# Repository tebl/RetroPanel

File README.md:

# RetroPanel
Having found a motherboard I really wanted to use, I found that obtaining an AT-case wasn't quite as easy as I had expected - at least none that met my demands for condition, price and availability anywhere near me. That's the short of it, see [Background](#2-background) for the full story. Anyway, my solution to my predicament was to simply use a slightly more modern ATX-case, but I wanted it to have all of the features available to even the earlies of computer generations available to me - that includes a working power switch, a turbo-switch and one of those awesome looking Mhz-displays. Add a clock and a temperature-sensor and it soon becomes apparent: such a thing, only had the potential to exist in my head.

So I made one.

The resulting computer isn't what I had originally intended to build, but I am quite happy with the results. There are better MBs, there are faster CPU options available and the graphics card will excite no other retro enthusiast other the one I grew into - however, it is exactly the *"right"* kind of slow for the games I remember. The *RetroPanel* was the missing piece to make all of that work, and with the wonders of *open-source* you should now have everything you need to build one as well.

- [1> Versions](#1-versions)
  - [1.1> RetroPanel](#11-retropanel)
- [2> Background](#2-background)
- [3> Resources](#3-resources)
- [4> Acknowledgements](#4-acknowledgements)

# 1> Versions
While there may only be one version of the RetroPanel for quite some time, but knowing myself and the fact that it has become a form factor that I really like - in time there will be more than one version of the RetroPanel. The differences will more than likely be in core functionality, not in terms of different faceplates that should already be catered for in the standard version.

| Module                            | Description                                      |
| --------------------------------- | ------------------------------------------------ | 
| [RetroPanel](#11-retropanel)      | Standard version

## 1.1> RetroPanel

The standard version of the RetroPanel, envisioned to provide most features found on cases from even the earlies of computer generations - that includes a working power switch, a turbo-switch and one of those awesome looking Mhz-displays. With options for installing modules for adding a clock (RTC) to it as well as a temperature-sensor (BMP280).

The standard version is composed of the following set of PCBs, in the cases of alternative faceplates you would only need the one that is suitable for your needs. Follow the documentation links for specific information related to each of them, note that the documentation on building one of these units this is covered through the documentation for the main PCB ([RetroPanel Module](https://github.com/tebl/BulkyMIDI-32/tree/main/BulkyMIDI-32%20Module)).

| PCB                 | # Required    | Description                        | Documentation                      | Order      |
| ---------------------- | ----------- | ---------------------------------- | ---------------------------------- | ---------- |
| [RetroPanel Module](https://github.com/tebl/RetroPanel/tree/main/RetroPanel%20Module) | 1 | Main module | [Documentation](https://github.com/tebl/RetroPanel/blob/main/RetroPanel%20Module/README.md), [BOM](https://github.com/tebl/RetroPanel/blob/main/RetroPanel%20Module/README.md#3-bom) | PCBWay
| [RetroPanel Front](https://github.com/tebl/RetroPanel/tree/main/RetroPanel%20Front) | 1 | Front-facing board holding components | [Documentation](https://github.com/tebl/RetroPanel/blob/main/RetroPanel%20Front/README.md), [BOM](https://github.com/tebl/RetroPanel/blob/main/RetroPanel%20Front/README.md#3-bom) | PCBWay
| [RetroPanel Side](https://github.com/tebl/RetroPanel/tree/main/RetroPanel%20Side) | 2 | Design for the sides, you need two of these. | [Documentation](https://github.com/tebl/RetroPanel/blob/main/RetroPanel%20Side/README.md) | PCBWay
| [RetroPanel Faceplate (FP1)](https://github.com/tebl/RetroPanel/tree/main/faceplates/RetroPanel%20FP1) | 1 | Faceplate that goes on the very front of the module, this has provisions for all switches and LEDs | [Documentation](https://github.com/tebl/RetroPanel/tree/main/faceplates/RetroPanel%20FP1) | PCBWay

# 2> Background
Recently I had the glorious idea of rebuilding the first PC I bought, it was a low-budget option put together from a list of parts in the later parts of 1995. Due to sheer luck I still had some driver disks that came with it, so I knew that what I was looking for was a motherboard with the model number *P51437P4/FMB* as well as a *Cirrus Logic 5436* graphics card. Surprisingly expensive, no doubt because noone had felt like keeping the super-cheap hardware options in the first place - additionally it was an AT-motherboard with one of those clocks that you couldn't exchange the battery for.

Why does that matter? It doesn't, but the next thing does: I couldn't find an AT-case that wasn't either horribly mangled, situated around a collectors more beloved hardware or any combination of the two. Well, that's not completely true - I found and bought a case, but it was thrown from every moving postal truck from Poland all the way up to where I live - bringing us back to the first point on my little list.

No doubt having already listened in on my internal dialogue, YouTube gave me a viewing recommendation for a video from [philscomputerlab](https://www.youtube.com/@philscomputerlab) - [Building the 486 DX2 66 Retro Sleeper DOS PC](https://youtu.be/9bqqpuJ7M_I). What I liked with it was that he gave me a viable option by gently reminding me that ATX-cases are still plentiful, they're even easier to match the aesthetics of as most of the little bits are still being sold. His solution for powering was to use an ATX to AT-cable and using a simple toggle switch as a power switch, as is the common way of doing it.

There's just one thing I don't like about that, is that a part of the designs of the ATX PSUs is telling the power-on circuit on your motherboard not to instantly turn it on again once a short has been detected on one of its power rails. Have you tried shorting a 35A power supply? It'll scare the crap out of you, possibly vaporizing something in the process. Add a latching switch and it may keep cycling until you remove the power lead.

I'm not saying that the RetroPanel in any way can be considered a safety precaution, because it haven't been tested enough to give you any other guarantee other than it having worked the one time I tried it. I still wouldn't keep a vintage computer powered without being in the room with it, but it gives me the peace of mind needed to turn my back long enough to fiddle with things such as this documentation.

# 3> Resources
The following resources where used as references when creating the RetroPanel, while they are in no particular order - you may find all of them interesting when looking for more information beyond what have been provided as part of this [GitHub-repository](https://github.com/tebl/RetroPanel). 

- [AT Power Pinout](http://www.hilmanind.com/pinouts/atpwr.htm)
- [ATX Power Pinout](https://www.etechnog.com/2022/03/atx-power-supply-pinout-diagram.html)
- [ATX Momentary Switch](https://www.instructables.com/Latching-Momentary-Switch-for-ATX-PSU-Conversion/)
- [PC power supply cables and connectors](http://www.playtool.com/pages/psuconnectors/connectors.html)
- [DIY POST Card](https://bbright.tripod.com/information/postcard.htm)
- [More POST Card information](https://www.minuszerodegrees.net/misc/post_cards.htm)

# 4> Acknowledgements
Everything comes from something, in particular when it comes to most of my electronics projects. I mainly build things I would like to own, often doing a respin to fit my own particular style and preferences. In many cases the hardest parts of the designs will already have been provided by people far more knowledgable than I. In particular the smart switch circuit, was adapted from [ATX Momentary Switch](https://www.instructables.com/Latching-Momentary-Switch-for-ATX-PSU-Conversion/).

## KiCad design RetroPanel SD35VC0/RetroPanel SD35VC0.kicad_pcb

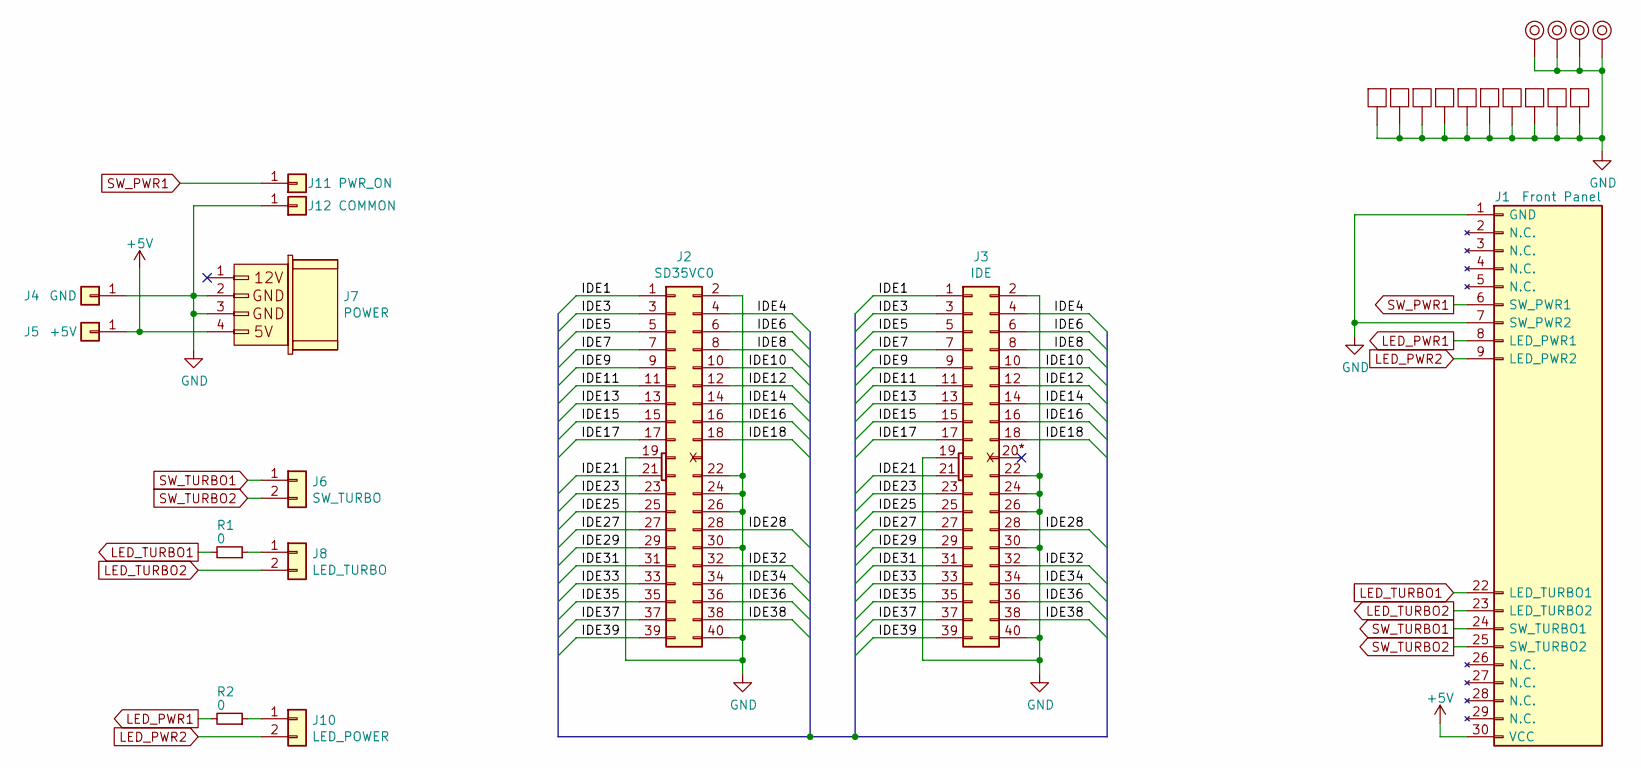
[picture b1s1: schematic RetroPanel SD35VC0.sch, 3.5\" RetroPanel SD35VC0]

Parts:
J1: Front Panel; SD35VC0_Module_Panel
J2: SD35VC0
J3: IDE; IDC-Header_2x20_P2.54mm_Vertical
J4: GND; PSU_Wire
J5: +5V; PSU_Wire
J6: SW_TURBO; PinHeader_1x02_P2.54mm_Vertical
J7: POWER; Molex_KK-254_1x04_P2.54mm_Horizontal
J8: LED_TURBO; PinHeader_1x02_P2.54mm_Vertical
J10: LED_POWER; PinHeader_1x02_P2.54mm_Vertical
J11: PWR_ON; PSU_Wire
J12: COMMON; PSU_Wire
M1, M2, M3, M16: Mounting_Pin; M3_pin
M5, M8, M9, M10, M11, M12, M13, M15: Mounting_Pad; Pad_pin
M7, M14: Mounting_Pad; B.Pad_pin
R1, R2: 0; R_Axial_DIN0207_L6.3mm_D2.5mm_P10.16mm_Horizontal

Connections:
+5V: J1.30 (VCC), J5.1, J7.4
/IDE1: J2.1, J3.1
/IDE3: J2.3, J3.3
/IDE4: J2.4, J3.4
/IDE5: J2.5, J3.5
/IDE6: J2.6, J3.6
/IDE7: J2.7, J3.7
/IDE8: J2.8, J3.8
/IDE9: J2.9, J3.9
/IDE10: J2.10, J3.10
/IDE11: J2.11, J3.11
/IDE12: J2.12, J3.12
/IDE13: J2.13, J3.13
/IDE14: J2.14, J3.14
/IDE15: J2.15, J3.15
/IDE16: J2.16, J3.16
/IDE17: J2.17, J3.17
/IDE18: J2.18, J3.18
/IDE21: J2.21, J3.21
/IDE23: J2.23, J3.23
/IDE25: J2.25, J3.25
/IDE27: J2.27, J3.27
/IDE28: J2.28, J3.28
/IDE29: J2.29, J3.29
/IDE31: J2.31, J3.31
/IDE32: J2.32, J3.32
/IDE33: J2.33, J3.33
/IDE34: J2.34, J3.34
/IDE35: J2.35, J3.35
/IDE36: J2.36, J3.36
/IDE37: J2.37, J3.37
/IDE38: J2.38, J3.38
/IDE39: J2.39, J3.39
GND: J1.1 (GND), J1.7 (SW_PWR2), J2.2, J2.19, J2.22, J2.24, J2.26, J2.30, J2.40, J3.2, J3.19, J3.22, J3.24, J3.26, J3.30, J3.40, J4.1, J7.2, J7.3, J12.1, M1.1, M2.1, M3.1, M5.1, M7.1, M8.1, M9.1, M10.1, M11.1, M12.1, M13.1, M14.1, M15.1, M16.1
LED_PWR1: J1.8 (LED_PWR1), R2.2
LED_PWR2: J1.9 (LED_PWR2), J10.2
LED_TURBO1: J1.22 (LED_TURBO1), R1.2
LED_TURBO2: J1.23 (LED_TURBO2), J8.2
unnamed: J8.1, R1.1
unnamed: J10.1, R2.1
SW_PWR1: J1.6 (SW_PWR1), J11.1
SW_TURBO1: J1.24 (SW_TURBO1), J6.1
SW_TURBO2: J1.25 (SW_TURBO2), J6.2

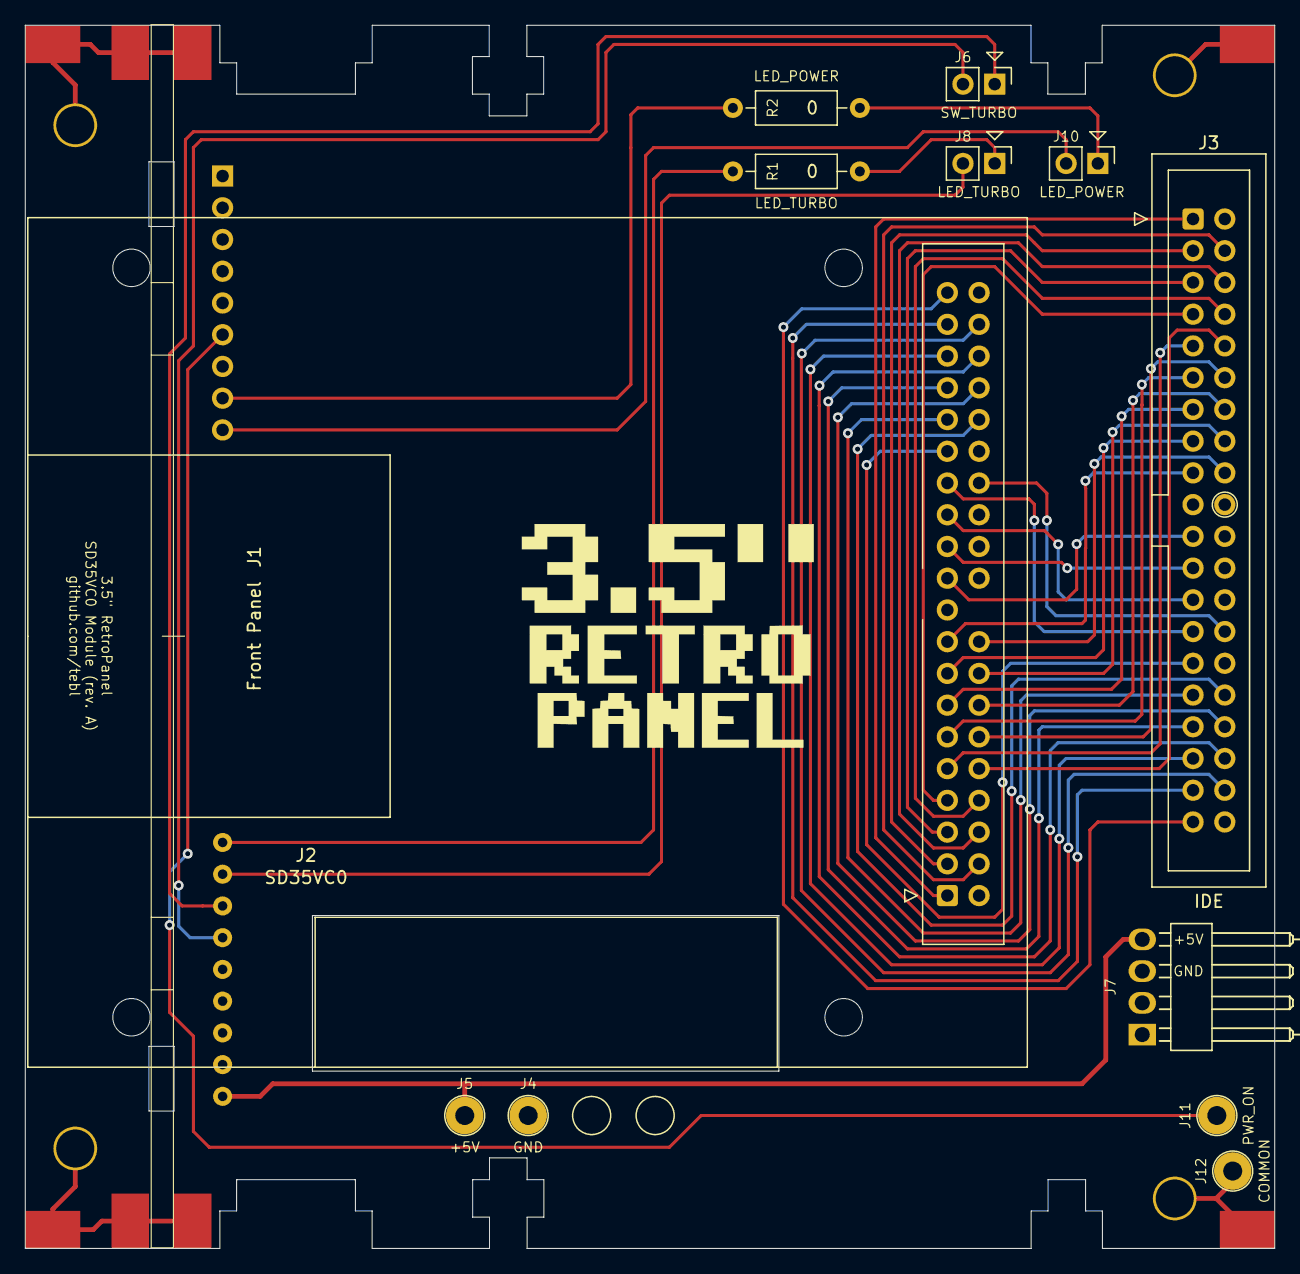
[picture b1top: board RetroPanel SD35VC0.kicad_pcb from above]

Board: 2 copper layers, 100.0 x 97.9 mm, 27 parts (0 on the bottom side), 43 nets.

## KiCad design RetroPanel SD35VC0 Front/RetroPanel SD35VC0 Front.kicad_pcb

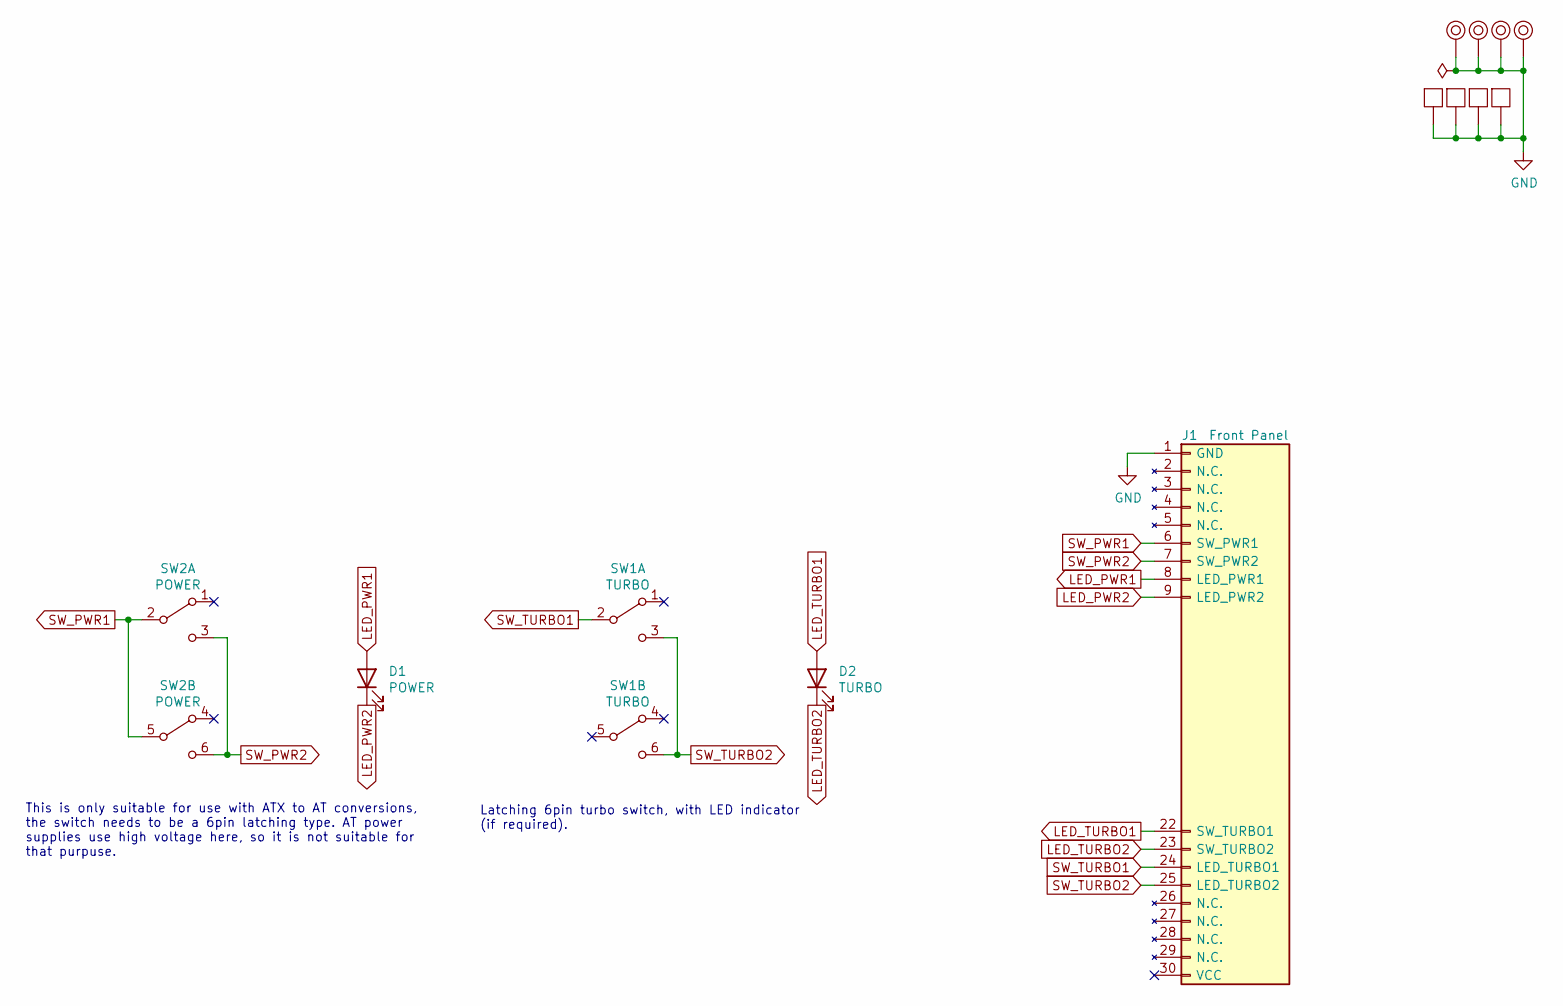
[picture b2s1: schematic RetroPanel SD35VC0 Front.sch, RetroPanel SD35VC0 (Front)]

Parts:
D1: POWER; LED_D5.0mm
D2: TURBO; LED_D5.0mm
J1: Front Panel; SD35VC0_PinHeader_1x30_P2.54mm_Horizontal
M1, M2, M3, M4: Mounting_Pin; M3_pin
M5, M7, M9, M10: Mounting_Pad; Pad_pin
SW1: TURBO; dpdt_switch_black
SW2: POWER; dpdt_switch_black

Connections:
GND: J1.1 (GND), M1.1, M2.1, M3.1, M4.1, M5.1, M7.1, M9.1, M10.1
LED_PWR1: D1.2 (A), J1.8 (LED_PWR1)
LED_PWR2: D1.1 (K), J1.9 (LED_PWR2)
LED_TURBO1: D2.2 (A), J1.22 (SW_TURBO1)
LED_TURBO2: D2.1 (K), J1.23 (SW_TURBO2)
SW_PWR1: J1.6 (SW_PWR1), SW2.2 (B), SW2.5 (B)
SW_PWR2: J1.7 (SW_PWR2), SW2.3 (C), SW2.6 (C)
SW_TURBO1: J1.24 (LED_TURBO1), SW1.2 (B)
SW_TURBO2: J1.25 (LED_TURBO2), SW1.3 (C), SW1.6 (C)

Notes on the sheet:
This is only suitable for use with ATX to AT conversions, the switch needs to be a 6pin latching type. AT power supplies use high voltage here, so it is not suitable for that purpuse.
Latching 6pin turbo switch, with LED indicator (if required).

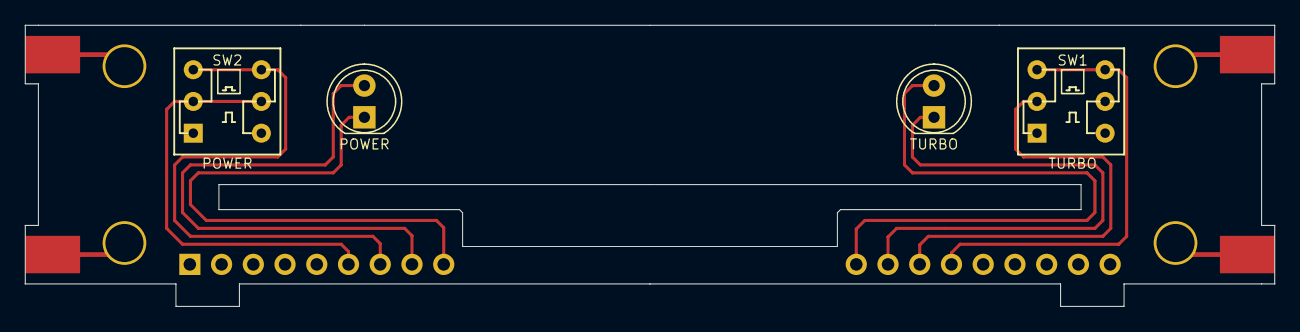
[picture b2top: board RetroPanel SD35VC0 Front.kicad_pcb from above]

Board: 2 copper layers, 100.0 x 22.5 mm, 13 parts (1 on the bottom side), 9 nets.

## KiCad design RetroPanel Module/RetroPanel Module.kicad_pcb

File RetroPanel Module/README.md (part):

# RetroPanel Module
The standard version of the RetroPanel consists of several separate PCB designs, five in total with two of these being the duplicated side panels. The piece of documentation you're currently looking at covers the main module as well as the overall build details, but take note that many of the other boards such as the [RetroPanel Front](https://github.com/tebl/RetroPanel/tree/main/RetroPanel%20Front) also comes with its own set of documenentation - so make sure that you browse around to get the full picture (especially when ordering parts). If you don't have any idea what all this is about, have a read through the [main documentation](https://github.com/tebl/RetroPanel) first.

- [1> Building the device](#1-building-the-device)
  - [1.1> Soldering it together](#11-soldering-it-together)
  - [1.2> Adding the front](#12-adding-the-front)
  - [1.3> Adding side panels](#13-adding-side-panels)
  - [1.4> Adding the cables](#14-adding-the-cables)
  - [1.5> Finishing touches](#15-finishing-touches)
- [2> Schematic](#2-schematic)
- [3> BOM](#3-bom)

# 1> Building the device
Building a device such as this assumes you have at least minor experience soldering things together, recommended is that you at the very least have access to a soldering station with adjustable temperature. If currently available, you should probably start with 60/40 rosin core solder as the lead-free alternatives tends to be a bit harder to work with.

With requirements for basic equipment sorted, we need to talk a bit about what you want to achieve while building this project. The reason I ask is that while you'll be able to find something for anyones taste in the project, at least provided that they enjoy building with vintage computer hardware. The following features can more or less be built separately:
- Panel for switches and LEDs missing from modern case
- Smart power switch
- One of the following:
    - External display for common ISA/PCI diagnostic cards
    - Arduino-driven display for use as a Mhz-display if needed, additionally the following features can be added to it:
      - Clock
      - Temperature display
      - RS-232 functionality for displaying information on the display, accessible through a simple serial interface.

Now that you know what you want to build, we can get started on the most expensive step in any build process - shopping! So, head on over to the [BOM](#3-bom)-section for some information on what kind of components that you'll need.

**NB!** While I would have liked to give you specific part numbers for "reputable" electronic part suppliers, I can't afford to shop there so I usually make due with what can be found on sites such as ebay, AliExpress and other sites that sell *cheap* chinese components. The downside to this is that I can't link to a part directly and expect it to stay listed, so you'll need to consider the description listed as mere *suggested search terms*.

## 1.1> Soldering it together
The construction of this unit should be fairly straight-forward, just take your time in order to make sure everything goes into place - more or less straight. I usually recommend starting by having a good look at the PCBs, try to figure out where all of the listed components go and in which orientation they go in (all of this should be clearly marked on the silkscreen).

While I would have liked to take every precaution and cover every possible combination of features, but for the purpose of keeping this document somewhat coherent - from this point on I'll mostly just assume that you're going to install every feature available. If you prefer something a little more visual, I've also taken the time to create a video in order to cover most of this - just click the image below.

If you only want parts of it, follow along on the schematic so that you know where each part are used. If you only wanted to use this as an external display for a diagnostic card, you'll generally only install the *J9*-connector for it and almost no other component. It can easily be combined with the smart switch, if you need that - it is separate from all of the Arduino-related circuitry.

In order to assure that the solder-jumpers are easy to set, it's a good idea to get those out of the way as the first we do - most of the information should be visible be in some form on your PCB (pin 1 out the 3 encountered will be square, with the others having a rounded shape). For example, the one marked *JP5* needs to be set according to the type of 7-segment display you've ordered, set it to *1-2* for CK (*Common Kathode*) or *2-3* for CA (*Common Anode*). *JP3* should be set to *1-2*. The safe choice for *JP1*, *JP2* and *JP4* is *2-3*, *2-3*, *2-3* though it won't be crucial unless you're building a cut-down version of the design.

When it comes to the components themselves, I will usually try to install them in the order according to their physical size. Doing it this way means you'll have an easier time keeping everything from looking crooked, but this is your board, your build and you want it perfect - don't you? If you said no, then go sit in the corner, because I worked hard on creating this for you.

I usually start by soldering in all of the resistors, ensuring that we're using the correct values in each of the positions. In some of the positions you will encounter the value specified as "0", or zero - these can be replaced with small pieces of wire. The reason that these exist is that a computer motherboard will likely expect an LED from that period in time, while you might be tempted to install something quite more modern in their place. The ones I'm referring to are usually sold as *"bright"* or *"clear"* LEDs, their efficiency is far higher than their old counterparts and for that reason you can install suitable resistors in these places to bring their brightness down (some may even require a value of 1k and above). All of that may require you to find and read the relevant datasheet, then do the needed math to find a suitable value. Or just do what I usually do: use the old style of coloured LEDs.

**NB!** Resistor *R23* directly next to the MAX232 is part of the MAX232-circuit, but you need to install it regardless of not wanting RS-232. The serial interface may have spurious issues working without it, so either add it - or - alternatively ensure that you disable the interface in the Arduino sketch before uploading it (*settings.h*).

The single diode marked *1n5819* is next, paying particular attention that the silver band of the component need to match that of the markings on the PCB. The purpose of it is to ensure that if you were to connect the USB-lead from the *Arduino Pro Micro* up to your modern laptop with the module installed in a different computer, this ensures that the Arduino won't attempt and more likely burn out while trying to power up the vintage PC. Meaning in theory you could replace it with a wire as can be shown in some of the gallery images, but this shouldn't be part of any kind of recommendation.

Sockets should be installed for the two ICs needed for the complete unit - you could probably manage without them if you know that you're using known good parts. However, they're cheap and you could probably afford to be quite so *cheap*!  I recommend tacking opposing corners into place, then reheat and push flush against the board before soldering the remaining pins.

Next to follow will be the non-polarized capacitors, the kind I use are mostly monolithic capacitors - mostly because I prefer their uniform look over the standard ceramic capacitors. Whatever the difference is, I have no idea beyond that so far they have worked as expected. The area around *U1*, the MAX232 chip, will have some rather peculiar-looking footprints - the reason for this is that the requirements are different for different versions of the chip - the slightly more expensive chip in the form of the MAX232**A** will want the regular 100nF capacitors and you should therefore add those now. The slightly cheaper is usually option will have something else as their first letter, usually a "**C**" though that stands for something else in the comparison - generally these will require polarized electrolytic capacitors added later. 

**NB!** Most electrolytic capacitors have a 100nF value (usually marked *104* directly on it), the ones that require a different value specifically have that printed on the board. Specifically I'm talking about *C8*, it is part of the smart switch and needs a value of 1000nF (this should me marked *105*).

Moving on we'll look at connectors, of which there are only two that we need to think about. As the Arduino is mutually exclusive with using the display with a diagnostic card, you'd only install *J9* when no Arduino is installed (I put my Arduino on a socket so that I can decide later). *J11* is used with RS-232, install if needed and intended. I prefer using IDC-connectors as those are properly keyed, but if you don't have any of the correct size available you may substitute them with regular straight pin-headers.

Speaking of capacitors, we'll just go ahead and install the polarized ones as well. If you opted for the cheaper variant of the MAX232-chip (the one not marked MAX232 and **A** as its first letter), there should be four of them close to this chip. Ideally you've not yet installed a bunch of non-polarized capacitors here already, if you have - then you either need to get the better chip or remove them. As polarized as they are, we need to ensure that these are always installed the right way around - the stripe on the side of the capacitor denotes the negative side of it, this should match the filled in (white) area on the footprint. When in doubt, the longer pin goes into the other hole - the one marked with an extremely tiny "+" next to it.

I usually tend to solder female pin-headers to modules that I want to remove later, such as the *Arduino Pro Micro*. The *Pro Micro* unfortunately comes in a slightly wider, and a more narrow version depending on what you're used to - this is the reason for the double set of pins on one side. When using female pin-headers on the module itself, this does not matter much. However when we instead intend to solder it straight to the board, you need to make sure to solder in the version that matches your board specifically. *A2* and *A3* we give the same treatment, they're for the *clock* and *temperature* modules that we have the option of adding.

While we're already dealing with pin-headers, just go ahead and all of those that we intend to a signal from the computers motherboard at some point. That should be all of those remaining, primarily the column directly under the *Arduino Pro Micro*. Personally I tend to use different coloured pin headers for those that will connect up to a LED compared to those going to switches, mostly so that I don't have to think so hard about what's going where. They'll never go in straight the first time, so just solder in the first pin - that way you can adjust them before soldering it all the way. You will burn your fingers doing at least one of them, that's the natural law of soldering short pin-header segments. 

## 1.2> Adding the front
Soldering together the front panel will be covered as part of its [documentation](https://github.com/tebl/RetroPanel/blob/main/RetroPanel%20Front/README.md#11-soldering-it-together), including a separate [BOM](https://github.com/tebl/RetroPanel/blob/main/RetroPanel%20Front/README.md#3-bom). Remembering that we earlier set some jumpers according to the display that was used, also - we remembered to use a latching power switch if we had decided against installing the smart switch circuit (momentary switch when it is used). As this needs to be added correctly, consider checking out the [assembly](https://youtu.be/NcJ1v0hauTQ?t=978)-video to see this chapter in action first.

With a completed front panel in front of you, it should easily slot into the main PCB - some resistance due to slightly crooked right-angle pin can be expected, but it shouldn't be an issue if you did your job well. When soldering it to the main board, just start with the opposing corners and ensure that it is at an almost perfect **90 degree angle**. While that sounds like something that'd be hard to do, you can easily use the sharp angle on your two side panels to check.

Do this for **both** of the outer edges!

When satisfied, solder the remaining pins. Using your most solid wire clippers to trim the excess of the pin headers from the underside.

**WARNING!** Do **NOT** use your standard side cutters as this will either dull them - OR - have them break in a spectacular fashion. By "*spectacular*" I mean sharp shrapnel, suddenly flying past your head. Failing that, at least use some sort of eye protection. 

## 1.3> Adding side panels
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
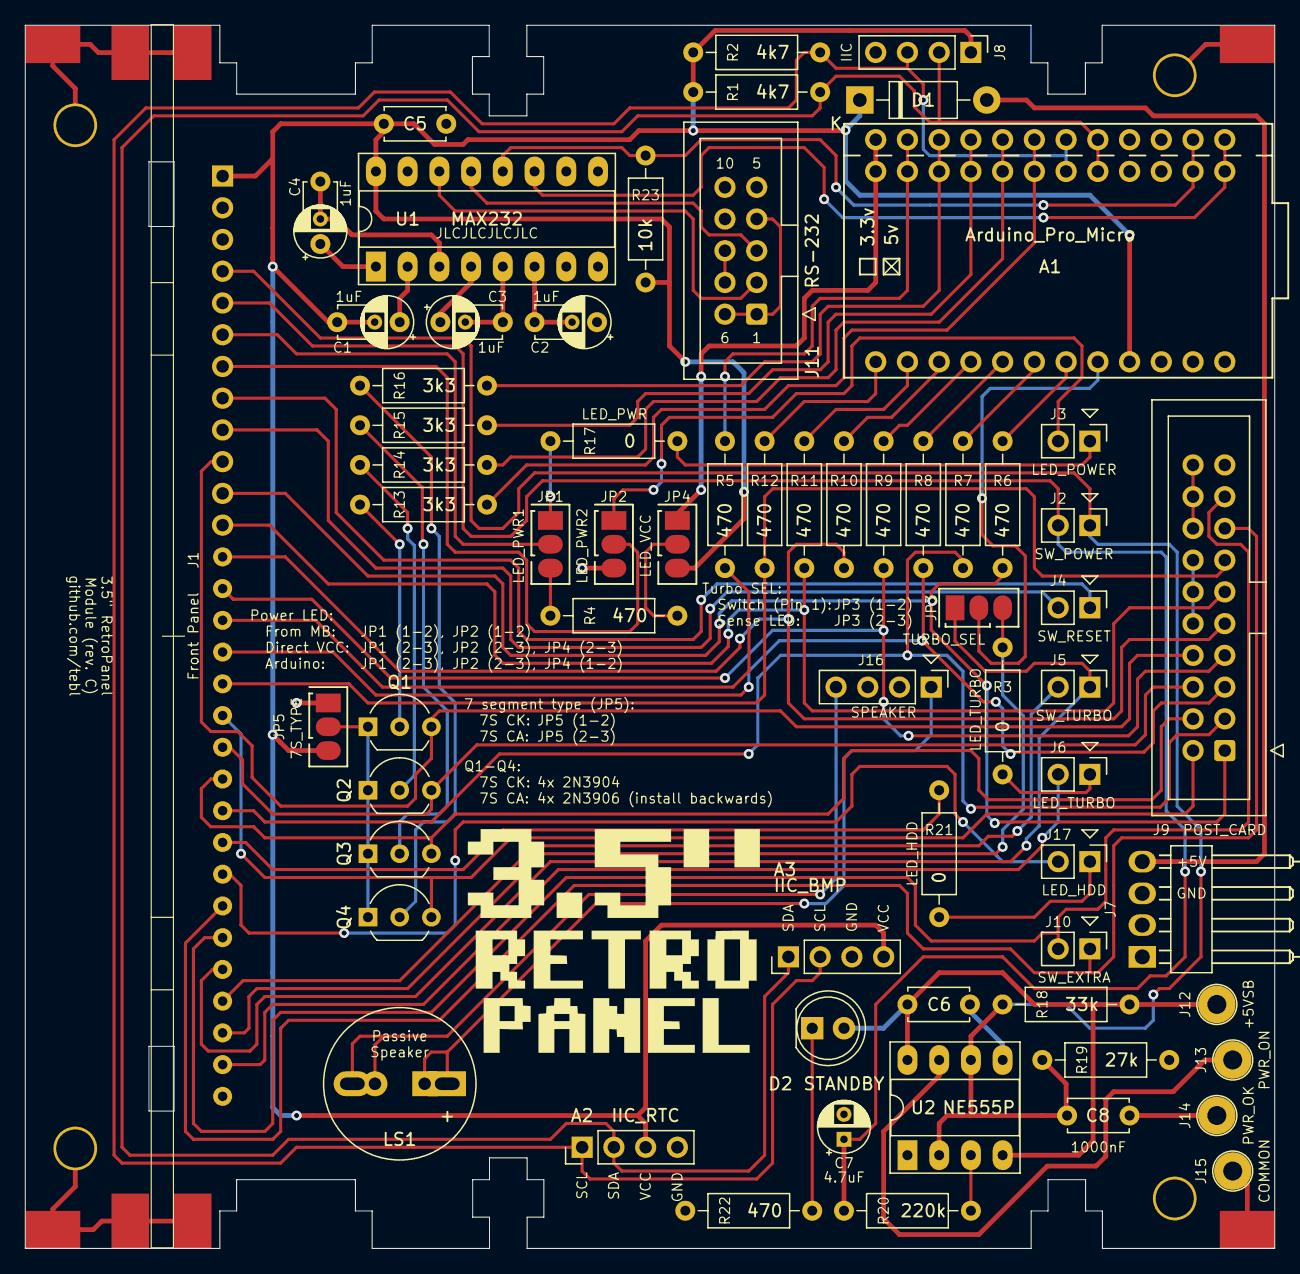
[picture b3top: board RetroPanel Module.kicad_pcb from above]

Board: 2 copper layers, 100.0 x 97.9 mm, 79 parts (0 on the bottom side), 79 nets.

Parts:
A1: Arduino_Pro_Micro
A2: IIC_RTC; DS3231_ZS-042
A3: IIC_BMP; BMP280-5V
C1, C2, C3, C4: 1uF; CP_Radial_D4.0mm_P2.00mm_Custom
C5, C6: 100nF; C_Disc_D4.7mm_W2.5mm_P5.00mm
C7: 4.7uF; CP_Radial_D4.0mm_P2.00mm
C8: 1000nF; C_Disc_D4.7mm_W2.5mm_P5.00mm
D1: 1N5819; D_DO-41_SOD81_P10.16mm_Horizontal
D2: STANDBY; LED_D5.0mm
J1: Front Panel; Module_Panel
J2: SW_POWER; PinHeader_1x02_P2.54mm_Vertical
J3: LED_POWER; PinHeader_1x02_P2.54mm_Vertical
J4: SW_RESET; PinHeader_1x02_P2.54mm_Vertical
J5: SW_TURBO; PinHeader_1x02_P2.54mm_Vertical
J6: LED_TURBO; PinHeader_1x02_P2.54mm_Vertical
J7: POWER; Molex_KK-254_1x04_P2.54mm_Horizontal
J8: IIC; PinHeader_1x04_P2.54mm_Vertical
J9: POST_CARD; IDC-Header_2x10_P2.54mm_Vertical
J10: SW_EXTRA; PinHeader_1x02_P2.54mm_Vertical
J11: RS-232; IDC-RS-232-Female
J12: +5VSB; PSU_Wire
J13: PWR_ON; PSU_Wire
J14: PWR_OK; PSU_Wire
J15: COMMON; PSU_Wire
J16: SPEAKER; PinHeader_1x04_P2.54mm_Vertical
J17: LED_HDD; PinHeader_1x02_P2.54mm_Vertical
JP1: LED_PWR1; select
JP2: LED_PWR2; select
JP3: TURBO_SEL; select
JP4: LED_VCC; select
JP5: 7S_TYPE; select
LS1: Passive Speaker; Buzzer_12x9.5RM7.6
M1, M2, M3, M16: Mounting_Pin; M3_pin
M5, M8, M9, M10, M11, M12, M13, M15: Mounting_Pad; Pad_pin
M7, M14: Mounting_Pad; B.Pad_pin
Q1, Q2, Q3, Q4: 2N3904 *; TO-92_Inline_Wide
R1, R2: 4k7; R_Axial_DIN0207_L6.3mm_D2.5mm_P10.16mm_Horizontal
R3, R17, R21: 0; R_Axial_DIN0207_L6.3mm_D2.5mm_P10.16mm_Horizontal
R4, R5, R6, R7, R8, R9, R10, R11, R12, R22: 470; R_Axial_DIN0207_L6.3mm_D2.5mm_P10.16mm_Horizontal
R13, R14, R15, R16: 3k3; R_Axial_DIN0207_L6.3mm_D2.5mm_P10.16mm_Horizontal
R18: 33k; R_Axial_DIN0207_L6.3mm_D2.5mm_P10.16mm_Horizontal
R19: 27k; R_Axial_DIN0207_L6.3mm_D2.5mm_P10.16mm_Horizontal
R20: 220k; R_Axial_DIN0207_L6.3mm_D2.5mm_P10.16mm_Horizontal
R23: 10k; R_Axial_DIN0207_L6.3mm_D2.5mm_P10.16mm_Horizontal
U1: MAX232; DIP-16_W7.62mm_Socket_LongPads
U2: NE555P; DIP-8_W7.62mm_Socket_LongPads

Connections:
+5V: A1.21, A2.3, A3.4, C1.2, C5.1, D1.1, J1.1, J8.1, JP4.3, JP5.3, R1.1, R2.2, R23.1, U1.16
/7S_A: J1.11, J9.1, R6.1
/7S_B: J1.21, J9.3, R7.1
/7S_C: J1.16, J9.5, R8.1
/7S_D: J1.14, J9.7, R9.1
/7S_D1: J1.10, J9.8, Q1.3
/7S_D2: J1.19, J9.6, Q2.3
/7S_D3: J1.20, J9.4, Q3.3
/7S_D4: J1.18, J9.2, Q4.3
/7S_DP: J1.15, R5.1
/7S_E: J1.13, J9.9, R10.1
/7S_F: J1.12, J9.11, R11.1
/7S_G: J1.17, J9.13, R12.1
/Smart Switch/+5VSB: C6.1, D2.2, J12.1, R18.2, U2.4, U2.8
/Smart Switch/PWR_OK: C8.1, J14.1
/Smart Switch/PWR_ON: J13.1, U2.7
ARD_PWR: A1.12, JP4.1
DIG1: A1.7, R13.1
DIG2: A1.8, R14.1
DIG3: A1.9, R15.1
DIG4: A1.10, R16.1
GND: A1.3, A1.4, A1.23, A2.4, A3.3, C2.1, C5.2, C7.2, J1.30, J7.2, J7.3, J8.4, J11.5, J15.1, JP2.3, JP5.1, M1.1, M2.1, M3.1, M5.1, M7.1, M8.1, M9.1, M10.1, M11.1, M12.1, M13.1, M14.1, M15.1, M16.1, R19.1, R22.1, U1.15, U2.1
IIC_SCL: A1.6, A2.1, A3.2, J8.3, R2.1
IIC_SDA: A1.5, A2.2, A3.1, J8.2, R1.2
LED_HDD1: J1.22, R21.2
LED_HDD2: J1.23, J17.2
LED_PWR1: J1.6, JP1.2
LED_PWR2: J1.7, JP2.2
LED_TURBO1: J1.28, JP3.3, R3.2
LED_TURBO2: J1.29, J6.2
unnamed: A1.11, R5.2
unnamed: A1.13, R12.2
unnamed: A1.14, R11.2
unnamed: A1.15, R10.2
unnamed: A1.16, R9.2
unnamed: A1.17, R8.2
unnamed: A1.18, R7.2
unnamed: A1.19, R6.2
unnamed: A1.20, JP3.2
unnamed: C1.1, U1.2
unnamed: C2.2, U1.6
unnamed: C3.1, U1.4
unnamed: C3.2, U1.5
unnamed: C4.1, U1.1
unnamed: C4.2, U1.3
unnamed: C6.2, U2.5
unnamed: D1.2, J7.4
unnamed: D2.1, R22.2
unnamed: J3.1, R17.2
unnamed: J3.2, JP2.1
unnamed: J6.1, R3.1
unnamed: J9.10, J9.12, J9.14
unnamed: J9.16, J9.18, J9.20
unnamed: J11.1, J11.4, J11.6
unnamed: J11.7, J11.8
unnamed: J16.1, LS1.1
unnamed: J16.4, LS1.2
unnamed: J17.1, R21.1
unnamed: JP1.1, R17.1
unnamed: JP1.3, R4.2
unnamed: JP4.2, R4.1
unnamed: JP5.2, Q1.1, Q2.1, Q3.1, Q4.1
unnamed: Q1.2, R13.2
unnamed: Q2.2, R14.2
unnamed: Q3.2, R15.2
unnamed: Q4.2, R16.2
unnamed: R20.2, U2.3
RS232_RX: J11.3, U1.13
RS232_TX: J11.2, U1.14
SW_EXTRA1: J1.24, J9.15, J10.1
SW_EXTRA2: J1.25, J9.17, J10.2
SW_PWR1: C8.2, J1.4, J2.1, R18.1, R19.2, U2.2, U2.6
SW_PWR2: C7.1, J1.5, J2.2, R20.1
SW_RESET1: J1.8, J4.1
SW_RESET2: J1.9, J4.2
SW_TURBO1: J1.26, J5.1, JP3.1
SW_TURBO2: J1.27, J5.2
TTL_RX: A1.2, R23.2, U1.12
TTL_TX: A1.1, U1.11

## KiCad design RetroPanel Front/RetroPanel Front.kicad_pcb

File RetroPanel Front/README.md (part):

# RetroPanel Front
This is a front-facing panel for controlling the *RetroPanel*, it holds all of the LEDs, switches as well as the 7-segment display associated with the RetroPanel itself. It mounts on the [RetroPanel Module](https://github.com/tebl/RetroPanel/tree/main/RetroPanel%20Module) using right-angle pin headers with slots cut into the PCBs to offer it some mechanical strength. The instructions for assembling one is mostly organized along with the main module, but the [BOM](#3-bom) included at the bottom of this document should be taken into account when ordering parts.

- [1> Building the device](#1-building-the-device)
  - [1.1> Soldering it together](#11-soldering-it-together)
- [2> Schematic](#2-schematic)
- [3> BOM](#3-bom)

# 1> Building the device
Building a device such as this assumes you have at least minor experience soldering things together, recommended is that you at the very least have access to a soldering station with adjustable temperature. If currently available, you should probably start with 60/40 rosin core solder as the lead-free alternatives tends to be a bit harder to work with.

With requirements for basic equipment sorted, we need to talk a bit about what you want to achieve while building this project. The reason I ask is that while you can build a *RetroPanel* with every feature available, it may not make sense for the computer it's going into. What I mean by that is that adding a turbo-switch wouldn't make sense unless your motherboard has a way of connecting it up. Have a read-through of the assembly instructions for the main [RetroPanel Module](https://github.com/tebl/RetroPanel/tree/main/RetroPanel%20Module) for a bit more details.

Now that you know what you want to build, we can get started on the most expensive step in any build process - shopping! So, head on over to the [BOM](#3-bom)-section for some information on what kind of components that you'll need. While I would have liked to give you specific part numbers for "reputable" electronic part suppliers, I can't afford to shop there so I usually make due with what I can find on sites such as ebay, AliExpress and any similar sites that sell cheap chinese components. The downside to this is that I can't link to a part directly and expect it to stay listed, so you'll need to consider the description listed as suggested search terms.

## 1.1> Soldering it together
The construction of this unit should be fairly straight-forward, just take your time in order to make sure everything goes into place - more or less straight. I usually recommend starting by having a good look at the PCBs, try to figure out where all of the listed components go and in which orientation they go in (all of this should be clearly marked on the silkscreen). The process of building it up should be covered in the assembly-video, click the picture below to jump directly to the relevant section.

The first component to go in, is a section of standard right-angle pin-headers - these are installed on the reverse of the PCB from what would otherwise be expected. The alignment must be done as neatly as you can, the easiest way of doing it is to soldering in a pin at each end - reheat and push the pin so that the plastic ends up sitting flush with the PCB. When satisfied with it, solder in the remaining pins.

Second is the switches that you need, these must have a black base at the bottom of them - this is important as the others will have a different pinout. Depending on the functionality that you need, some of these must be latching (*turbo*-switch in particular) while others must be non-latching (*reset* and the *tool*-button in particular). The power switch is a special case as it can be either, generally you want the latching variety when main unit is built **without** the smart power switch circuitry - in any other case you may prefer to use the switch already on your ATX-case.

The switches themselves has six pins and it may not be directly evident which of them is pin 1, so one common error is installing these upside down. Looking a bit closer at them you may observe that there is a square hole on the underside of them that is closer to one side, this is the square shown on the silkscreen. To avoid binding on the switches, take some care to get them sitting straight.

A faceplate is mounted on the top of the front, with 10mm hex standoffs between the two - in order to get the positioning of the LEDs correct, you should add them to the outside corners and fix them in place using M3 nuts.

Depending on what features you wanted to use it with, you may require up to three standard 5mm LEDs - these should be roughly put into place in their holes without soldering them into place. Longer pin of the LED goes into the round-shaped pad on the PCB. Temporarily adding the faceplate into place on top, allow the LEDs to fall into the cutouts made for them - only then, do you solder them into their place.

The 7-segment display can be added to the module in a couple of ways, at least two ways that I've though of so far:
- The first is to solder female machined header pins to the PCB, then insert a display with shortened pins into the header pins. This does include the joys of dealing with female machined pins such as those usually found on sockets, but at the advantage of being able to easily change out or replace the display later.
- The other is to align the display with the inside edge of the faceplate, that way the pins of the display should almost poke through to the back of the PCB. Filling the holes with a controlled amount of solder should still allow a good connection, just allow it to flow completely through to the front edge of it. 

In either case, if you cant seem to get the display to fit through the cutout on the faceplate you may need to shave a bit off the inside edges with a sharp disposable blade. The reason for this is that PCB fabrication tend to be less exact when dealing with inside edges such as these. Additionally you may find that it also becomes easier once the plastic film on the front of the displays have either been removed, or slightly trimmed down to fit the outline better (I think it's supposed to be removed, but I don't know for sure).

That should be all there is to it when it comes to assembling the front panel, for actually installing it on the main module - jump on over to the main assembly [documentation](https://github.com/tebl/RetroPanel/blob/main/RetroPanel%20Module/README.md#12-adding-the-front).

# 2> Schematic
The supplied KiCad files should be sufficient as both a schematic and as a  starting point for ordering PCBs (basically you could just zip the contents of the export folder and upload that on a fabrication site), the schematic is also available in [PDF-format](https://github.com/tebl/RetroPanel/tree/main/documentation/schematic) and this is what you'll need to print and work your way through this things don't work as expected after assembly.

# 3> BOM
Most parts should be easy to get a hold of from your favourite local electronic component shop, but given that I don't have access to such shops where I live so everything was based on whatever I could get cheapest from eBay/AliExpress (free shipping, but plan on waiting 3-4 weeks for delivery). Normally I would specify the number of components in parenthesis that can be considered optional for features beyond the more basic functionality, but at this point you should already have a concise idea of what you're going to need.

| Reference             | Item                                                              | Count | Order  |
| --------------------- | ----------------------------------------------------------------- | ----- | ------ |
| Panel PCB             | Fabricate using Gerber files                                      |     1 | PCBWay
| D1-D3                 | 5mm LEDs, preferably frosted or solid colour (not the bright clear ones)          |     3 |
| J1                    | Breakable right-angle pin headers                                  |     1 |
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
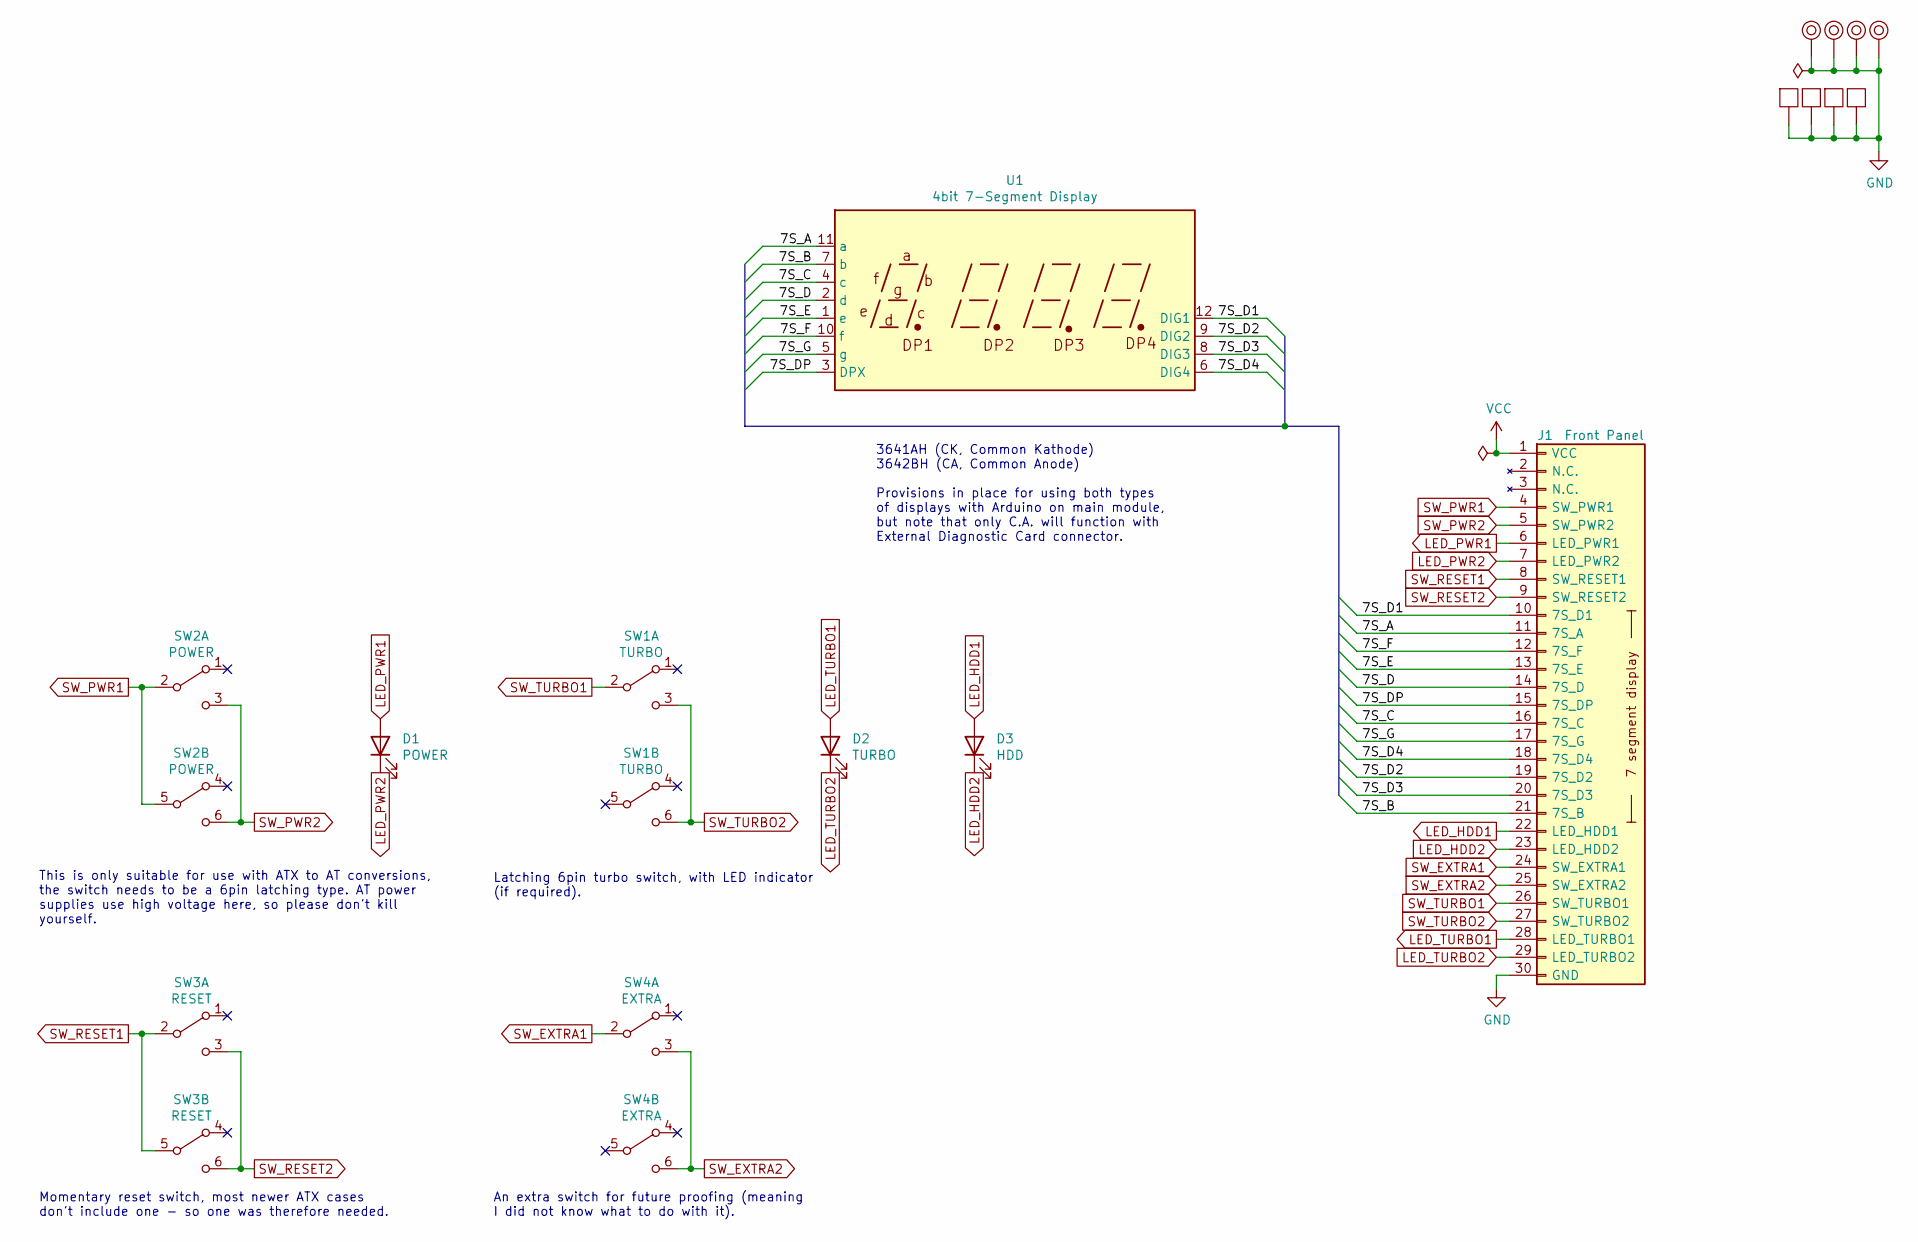
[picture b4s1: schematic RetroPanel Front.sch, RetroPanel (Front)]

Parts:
D1: POWER; LED_D5.0mm
D2: TURBO; LED_D5.0mm
D3: HDD; LED_D5.0mm
J1: Front Panel; PinHeader_1x30_P2.54mm_Horizontal
M1, M2, M3, M4: Mounting_Pin; M3_pin
M5, M7, M9, M10: Mounting_Pad; Pad_pin
SW1: TURBO; dpdt_switch_black
SW2: POWER; dpdt_switch_black
SW3: RESET; dpdt_switch_black
SW4: EXTRA; dpdt_switch_black
U1: 4bit 7-Segment Display; 3641AH

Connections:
/7S_A: J1.11 (7S_A), U1.11 (a)
/7S_B: J1.21 (7S_B), U1.7 (b)
/7S_C: J1.16 (7S_C), U1.4 (c)
/7S_D: J1.14 (7S_D), U1.2 (d)
/7S_D1: J1.10 (7S_D1), U1.12 (DIG1)
/7S_D2: J1.19 (7S_D2), U1.9 (DIG2)
/7S_D3: J1.20 (7S_D3), U1.8 (DIG3)
/7S_D4: J1.18 (7S_D4), U1.6 (DIG4)
/7S_DP: J1.15 (7S_DP), U1.3 (DPX)
/7S_E: J1.13 (7S_E), U1.1 (e)
/7S_F: J1.12 (7S_F), U1.10 (f)
/7S_G: J1.17 (7S_G), U1.5 (g)
GND: J1.30 (GND), M1.1, M2.1, M3.1, M4.1, M5.1, M7.1, M9.1, M10.1
LED_HDD1: D3.2 (A), J1.22 (LED_HDD1)
LED_HDD2: D3.1 (K), J1.23 (LED_HDD2)
LED_PWR1: D1.2 (A), J1.6 (LED_PWR1)
LED_PWR2: D1.1 (K), J1.7 (LED_PWR2)
LED_TURBO1: D2.2 (A), J1.28 (LED_TURBO1)
LED_TURBO2: D2.1 (K), J1.29 (LED_TURBO2)
SW_EXTRA1: J1.24 (SW_EXTRA1), SW4.2 (B)
SW_EXTRA2: J1.25 (SW_EXTRA2), SW4.3 (C), SW4.6 (C)
SW_PWR1: J1.4 (SW_PWR1), SW2.2 (B), SW2.5 (B)
SW_PWR2: J1.5 (SW_PWR2), SW2.3 (C), SW2.6 (C)
SW_RESET1: J1.8 (SW_RESET1), SW3.2 (B), SW3.5 (B)
SW_RESET2: J1.9 (SW_RESET2), SW3.3 (C), SW3.6 (C)
SW_TURBO1: J1.26 (SW_TURBO1), SW1.2 (B)
SW_TURBO2: J1.27 (SW_TURBO2), SW1.3 (C), SW1.6 (C)

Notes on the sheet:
This is only suitable for use with ATX to AT conversions, the switch needs to be a 6pin latching type. AT power supplies use high voltage here, so please don't kill yourself.
Latching 6pin turbo switch, with LED indicator (if required).
Momentary reset switch, most newer ATX cases don't include one - so one was therefore needed.
An extra switch for future proofing (meaning I did not know what to do with it).
3641AH (CK, Common Kathode) 3642BH (CA, Common Anode) Provisions in place for using both types of displays with Arduino on main module, but note that only C.A. will function with External Diagnostic Card connector.

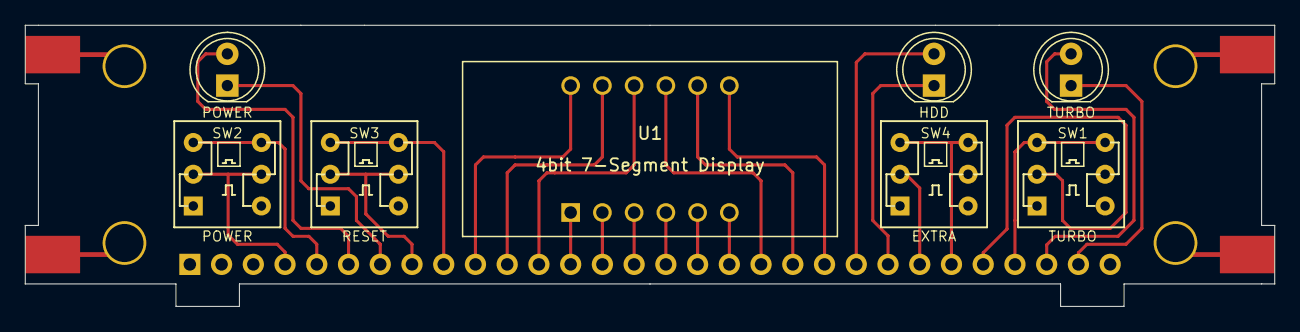
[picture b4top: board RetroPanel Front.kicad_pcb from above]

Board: 2 copper layers, 100.0 x 22.5 mm, 17 parts (1 on the bottom side), 27 nets.

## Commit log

2022-10-25 Front panel
2022-10-25 Layout first draft
2022-10-26 Add extra switch and tweak size
2022-10-26 Add mounting pads
2022-10-26 Add side panel
2022-10-26 Match grid
2022-10-27 Rough layout of module
2022-10-28 First schematic draft
2022-10-30 First layout draft done
2022-10-30 Small tweaks
2022-10-30 Faceplate FP1 and HDD LED
2022-10-31 FP1 icons
2022-10-31 Export files
2022-11-07 Moved power diode
2022-11-07 Bumped version
2022-11-08 Show segments
2022-11-08 Changed 7s display routine
2022-11-08 Handle DP differently
2022-11-08 Add datasheet
2022-11-08 README stub
2022-11-08 Simple console and EEPROM storage
2022-11-08 Can read messages from storage and test them
2022-11-09 Can update strings
2022-11-09 Tweak display cutout
2022-11-09 Can use both types of displays
2022-11-09 Better description for CA display usage
2022-11-10 Display commands
2022-11-10 Missing file
2022-11-11 Now actually works with both displays
2022-11-11 Tweaked resistor value to work better 7S CA
2022-11-12 Adjustable mounting with huge pads
2022-11-12 Optional standby power LED
2022-11-12 Fixed RS-232 connector and export files for second prototype
2022-11-15 Respond to serial port sending request
2022-11-16 Support for DS3231 RTC
2022-11-16 Can enable or disable rs232
2022-11-16 Tweak formatting
2022-11-16 Add external pullup for Serial1 RX
2022-12-01 Add mounting spot for DS3231 directly
2023-01-03 Adjust cutout to move unit forward
2023-01-03 BMP280 added
2023-01-03 Build images
2023-01-03 Move definition
2023-01-04 Change standby time
2023-01-11 Silkscreen tweaks
2023-01-11 Changed defaults to turbo off and rs232 on
2023-01-11 Refill
2023-01-19 Add images
2023-01-19 First draft of README
2023-01-19 Fix typos
2023-01-22 Add first draft of module README
2023-01-23 Faceplate tweaks (non-visible)
2023-01-23 Faceplate README
2023-01-28 SD35VC0 sketched out
2023-01-29 SD35VC0 Front sketched out
2023-01-31 Changed SW_PWR to pads for cable as it probably should be
2023-02-06 Add some links to assembly video
2023-02-06 Some documentation
2023-02-06 Shorten lower lip
2023-02-06 Removed unused files
2023-02-07 Faceplate
2023-02-07 Change schematic text
2023-02-07 Add missing files
2023-02-15 Sketch README
2023-02-23 Adjust faceplate cutouts
